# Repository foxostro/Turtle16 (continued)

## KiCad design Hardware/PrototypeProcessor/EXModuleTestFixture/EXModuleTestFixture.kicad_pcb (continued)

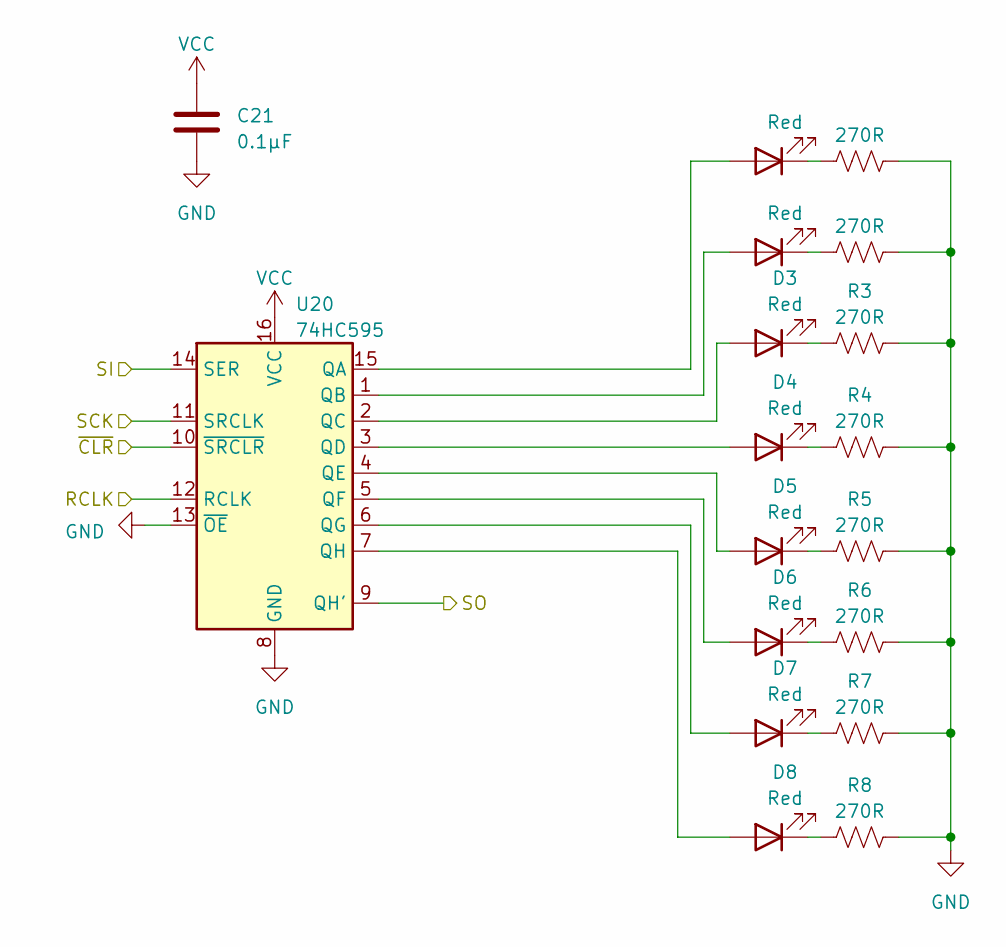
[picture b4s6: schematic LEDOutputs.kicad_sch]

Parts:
C21: 0.1µF; C_0603_1608Metric
D1, D2, D3, D4, D5, D6, D7, D8: Red; LED_0603_1608Metric
R1, R2, R3, R4, R5, R6, R7, R8: 270R; C_0603_1608Metric
U20: 74HC595; TSSOP-16_4.4x5mm_P0.65mm

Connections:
/LED Output/RCLK: U20.12 (RCLK); also elsewhere on the board
/LED Output/SCK: U20.11 (SRCLK); also elsewhere on the board
/LED Output/SI: U20.14 (SER); also elsewhere on the board
/LED Output/SO: U20.9 (QH')
/LED Output/~CLR: U20.10 (~SRCLR); also elsewhere on the board
GND: C21.2, R1.2, R2.2, R3.2, R4.2, R5.2, R6.2, R7.2, R8.2, U20.8 (GND), U20.13 (~OE); also elsewhere on the board
unnamed: D1.2 (A), U20.15 (QA)
unnamed: D1.1 (K), R1.1
unnamed: D2.2 (A), U20.1 (QB)
unnamed: D2.1 (K), R2.1
unnamed: D3.2 (A), U20.2 (QC)
unnamed: D3.1 (K), R3.1
unnamed: D4.2 (A), U20.3 (QD)
unnamed: D4.1 (K), R4.1
unnamed: D5.2 (A), U20.4 (QE)
unnamed: D5.1 (K), R5.1
unnamed: D6.2 (A), U20.5 (QF)
unnamed: D6.1 (K), R6.1
unnamed: D7.2 (A), U20.6 (QG)
unnamed: D7.1 (K), R7.1
unnamed: D8.2 (A), U20.7 (QH)
unnamed: D8.1 (K), R8.1
VCC: C21.1, U20.16 (VCC); also elsewhere on the board

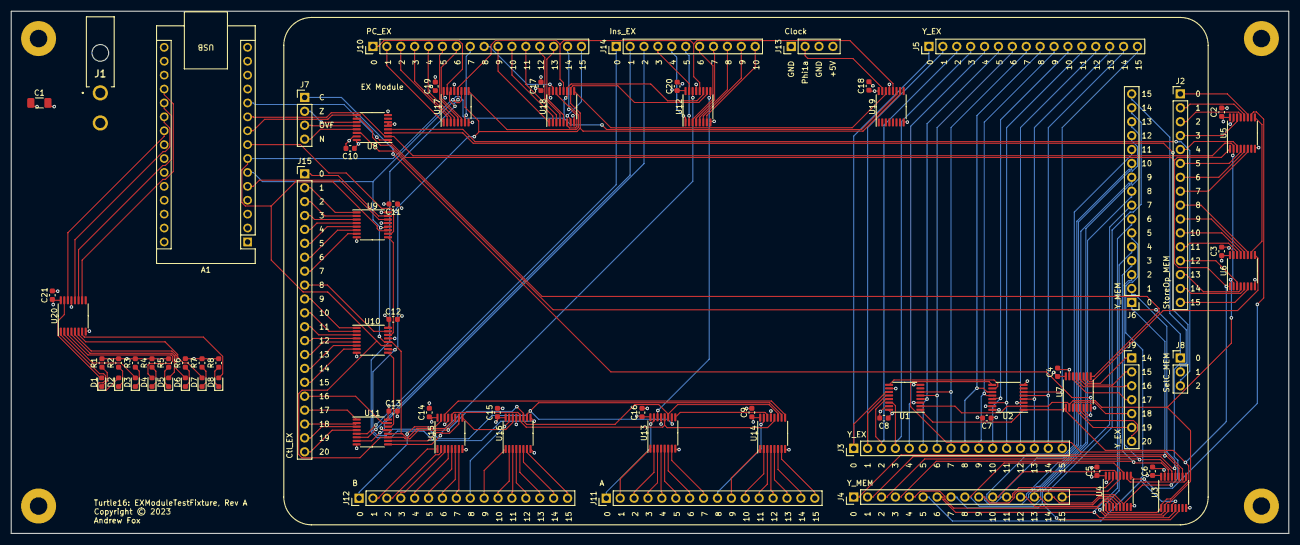
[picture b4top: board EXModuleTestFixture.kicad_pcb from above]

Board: 4 copper layers, 233.4 x 95.4 mm, 77 parts (0 on the bottom side), 189 nets.

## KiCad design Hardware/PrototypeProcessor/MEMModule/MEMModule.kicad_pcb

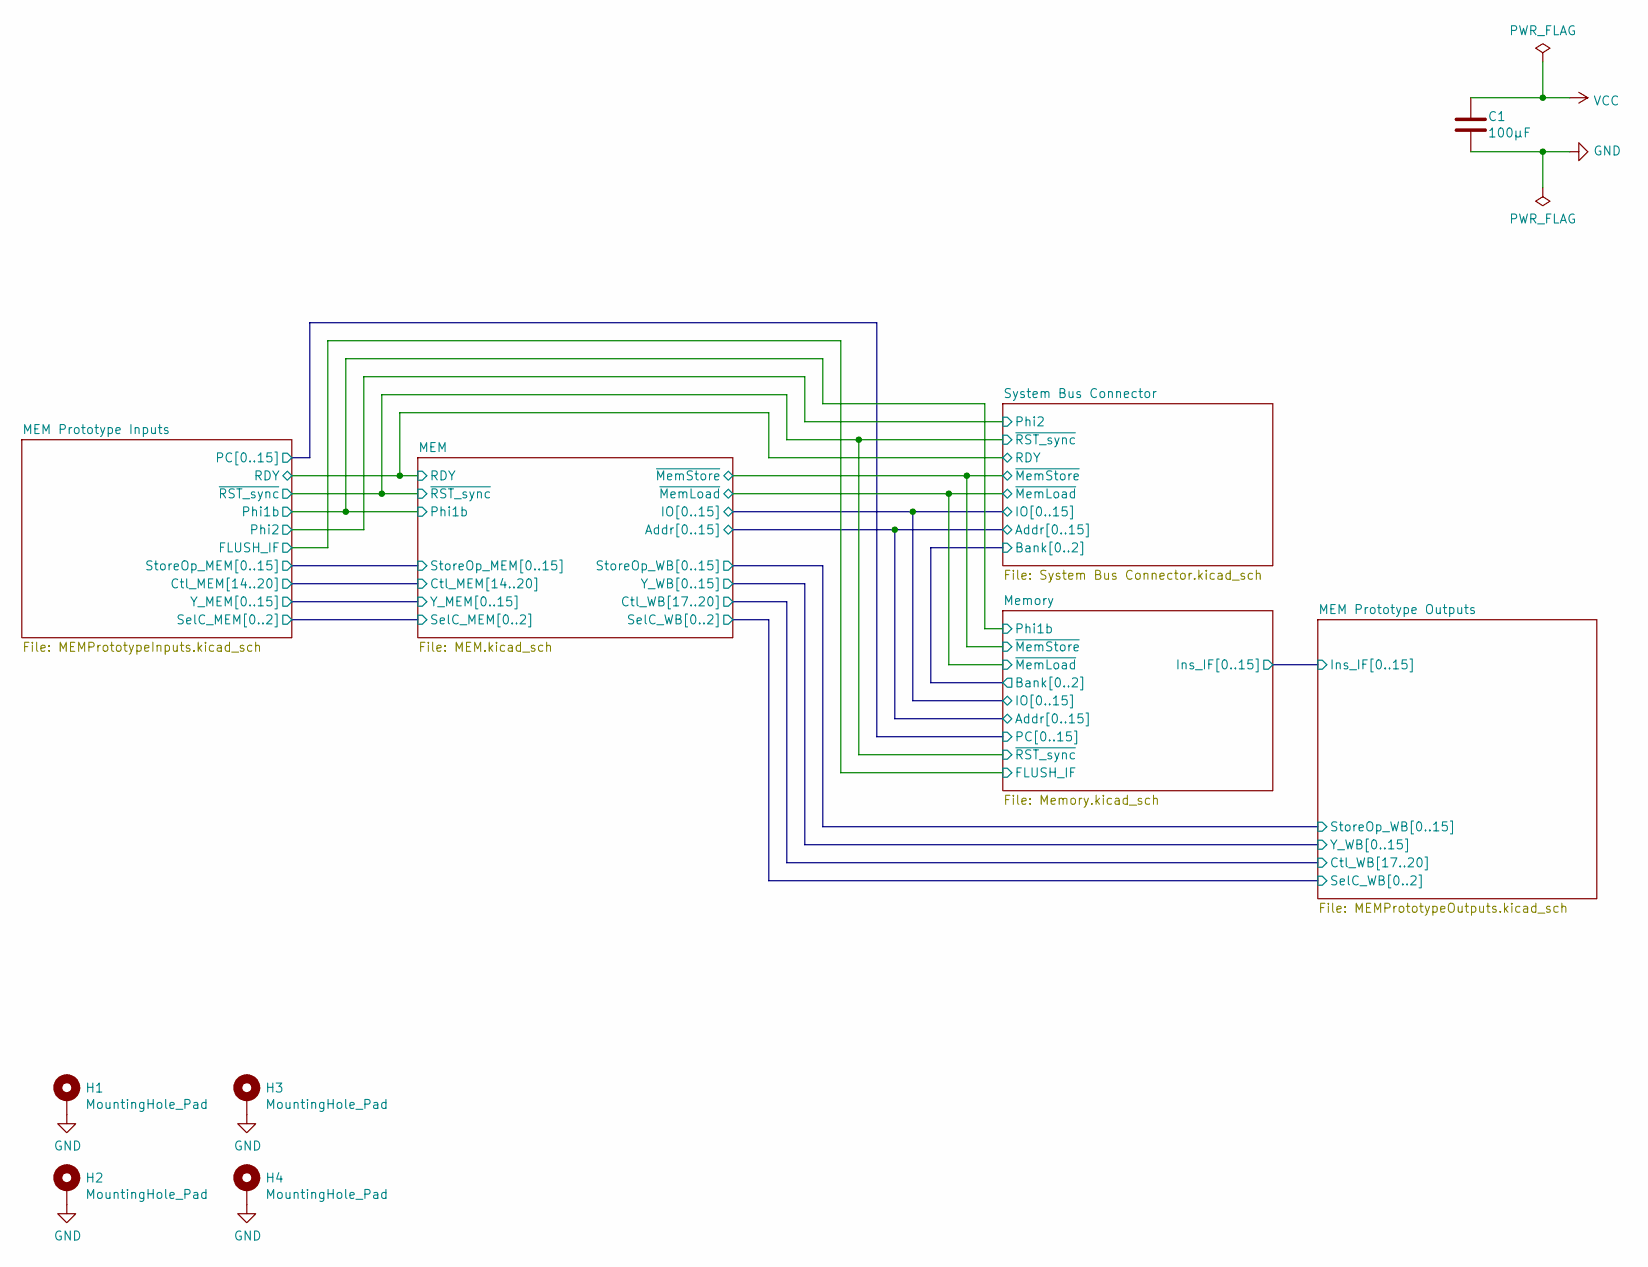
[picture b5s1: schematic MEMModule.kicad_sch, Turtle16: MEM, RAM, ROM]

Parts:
C1: 100µF; C_1206_3216Metric_Pad1.33x1.80mm_HandSolder
H1, H2, H3, H4: MountingHole_Pad; MountingHole_3.2mm_M3_Pad

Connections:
GND: C1.2, H1.1, H2.1, H3.1, H4.1; also elsewhere on the board
VCC: C1.1; also elsewhere on the board

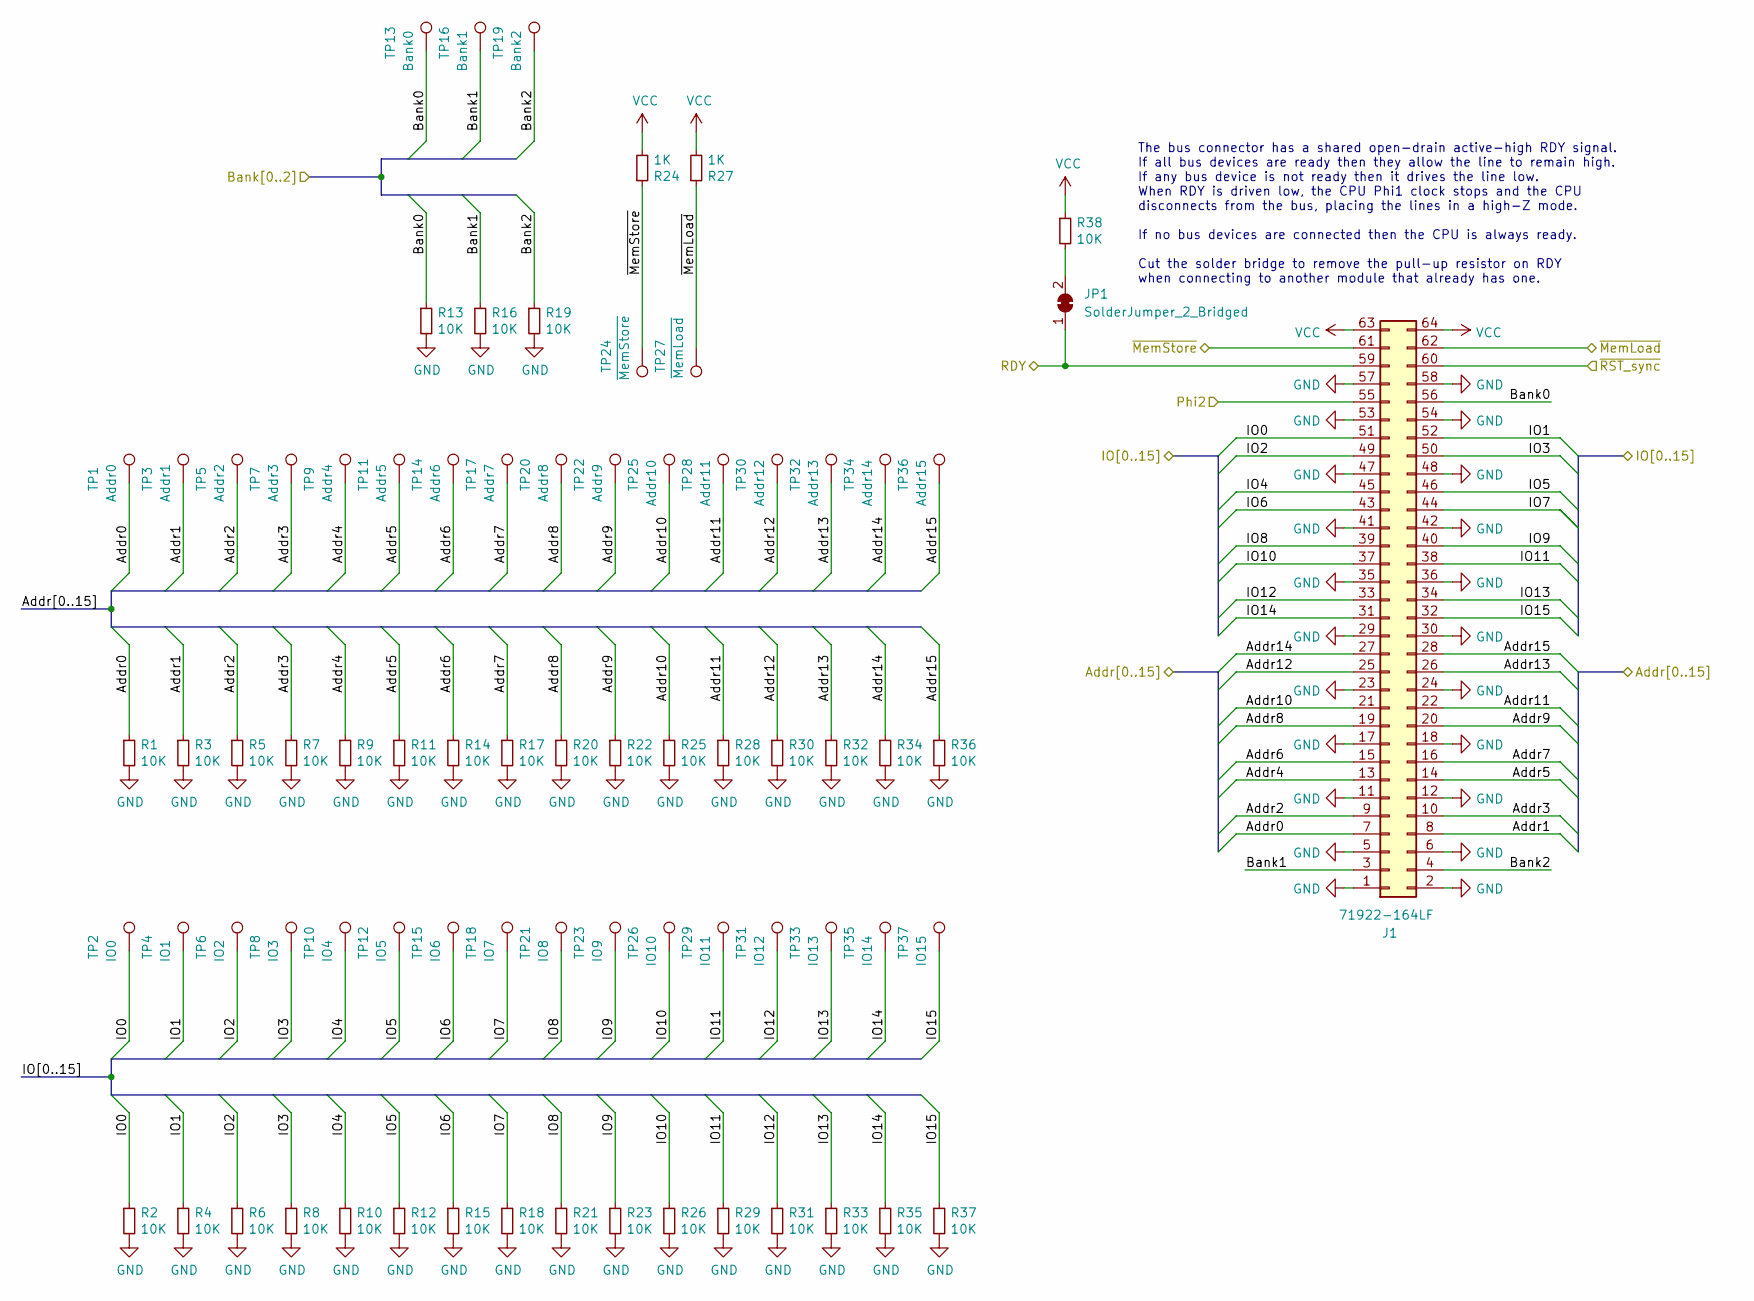
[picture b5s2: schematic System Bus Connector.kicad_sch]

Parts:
J1: 71922-164LF; IDC-Header_2x32_P2.54mm_Horizontal
JP1: SolderJumper_2_Bridged; SolderJumper-2_P1.3mm_Bridged_RoundedPad1.0x1.5mm
R1, R2, R3, R4, R5, R6, R7, R8, R9, R10, R11, R12, R13, R14, R15, R16, R17, R18, R19, R20, R21, R22, R23, R25, R26, R28, R29, R30, R31, R32, R33, R34, R35, R36, R37, R38: 10K; R_0603_1608Metric_Pad0.98x0.95mm_HandSolder
R24, R27: 1K; R_0603_1608Metric_Pad0.98x0.95mm_HandSolder
TP1: Addr0; TestPoint_Pad_D1.0mm
TP2: IO0; TestPoint_Pad_D1.0mm
TP3: Addr1; TestPoint_Pad_D1.0mm
TP4: IO1; TestPoint_Pad_D1.0mm
TP5: Addr2; TestPoint_Pad_D1.0mm
TP6: IO2; TestPoint_Pad_D1.0mm
TP7: Addr3; TestPoint_Pad_D1.0mm
TP8: IO3; TestPoint_Pad_D1.0mm
TP9: Addr4; TestPoint_Pad_D1.0mm
TP10: IO4; TestPoint_Pad_D1.0mm
TP11: Addr5; TestPoint_Pad_D1.0mm
TP12: IO5; TestPoint_Pad_D1.0mm
TP13: Bank0; TestPoint_Pad_D1.0mm
TP14: Addr6; TestPoint_Pad_D1.0mm
TP15: IO6; TestPoint_Pad_D1.0mm
TP16: Bank1; TestPoint_Pad_D1.0mm
TP17: Addr7; TestPoint_Pad_D1.0mm
TP18: IO7; TestPoint_Pad_D1.0mm
TP19: Bank2; TestPoint_Pad_D1.0mm
TP20: Addr8; TestPoint_Pad_D1.0mm
TP21: IO8; TestPoint_Pad_D1.0mm
TP22: Addr9; TestPoint_Pad_D1.0mm
TP23: IO9; TestPoint_Pad_D1.0mm
TP24: ~{MemStore}; TestPoint_Pad_D1.0mm
TP25: Addr10; TestPoint_Pad_D1.0mm
TP26: IO10; TestPoint_Pad_D1.0mm
TP27: ~{MemLoad}; TestPoint_Pad_D1.0mm
TP28: Addr11; TestPoint_Pad_D1.0mm
TP29: IO11; TestPoint_Pad_D1.0mm
TP30: Addr12; TestPoint_Pad_D1.0mm
TP31: IO12; TestPoint_Pad_D1.0mm
TP32: Addr13; TestPoint_Pad_D1.0mm
TP33: IO13; TestPoint_Pad_D1.0mm
TP34: Addr14; TestPoint_Pad_D1.0mm
TP35: IO14; TestPoint_Pad_D1.0mm
TP36: Addr15; TestPoint_Pad_D1.0mm
TP37: IO15; TestPoint_Pad_D1.0mm

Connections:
/MEM Prototype Inputs/Phi2: J1.55; also elsewhere on the board
/MEM Prototype Inputs/RDY: J1.59, JP1.1 (A); also elsewhere on the board
/MEM Prototype Inputs/~RST_sync: J1.60; also elsewhere on the board
/Memory/Addr0: J1.7, R1.1, TP1.1; also elsewhere on the board
/Memory/Addr1: J1.8, R3.1, TP3.1; also elsewhere on the board
/Memory/Addr2: J1.9, R5.1, TP5.1; also elsewhere on the board
/Memory/Addr3: J1.10, R7.1, TP7.1; also elsewhere on the board
/Memory/Addr4: J1.13, R9.1, TP9.1; also elsewhere on the board
/Memory/Addr5: J1.14, R11.1, TP11.1; also elsewhere on the board
/Memory/Addr6: J1.15, R14.1, TP14.1; also elsewhere on the board
/Memory/Addr7: J1.16, R17.1, TP17.1; also elsewhere on the board
/Memory/Addr8: J1.19, R20.1, TP20.1; also elsewhere on the board
/Memory/Addr9: J1.20, R22.1, TP22.1; also elsewhere on the board
/Memory/Addr10: J1.21, R25.1, TP25.1; also elsewhere on the board
/Memory/Addr11: J1.22, R28.1, TP28.1; also elsewhere on the board
/Memory/Addr12: J1.25, R30.1, TP30.1; also elsewhere on the board
/Memory/Addr13: J1.26, R32.1, TP32.1; also elsewhere on the board
/Memory/Addr14: J1.27, R34.1, TP34.1; also elsewhere on the board
/Memory/Addr15: J1.28, R36.1, TP36.1; also elsewhere on the board
/Memory/Bank0: J1.56, R13.1, TP13.1; also elsewhere on the board
/Memory/Bank1: J1.3, R16.1, TP16.1; also elsewhere on the board
/Memory/Bank2: J1.4, R19.1, TP19.1; also elsewhere on the board
/Memory/IO0: J1.51, R2.1, TP2.1; also elsewhere on the board
/Memory/IO1: J1.52, R4.1, TP4.1; also elsewhere on the board
/Memory/IO2: J1.49, R6.1, TP6.1; also elsewhere on the board
/Memory/IO3: J1.50, R8.1, TP8.1; also elsewhere on the board
/Memory/IO4: J1.45, R10.1, TP10.1; also elsewhere on the board
/Memory/IO5: J1.46, R12.1, TP12.1; also elsewhere on the board
/Memory/IO6: J1.43, R15.1, TP15.1; also elsewhere on the board
/Memory/IO7: J1.44, R18.1, TP18.1; also elsewhere on the board
/Memory/IO8: J1.39, R21.1, TP21.1; also elsewhere on the board
/Memory/IO9: J1.40, R23.1, TP23.1; also elsewhere on the board
/Memory/IO10: J1.37, R26.1, TP26.1; also elsewhere on the board
/Memory/IO11: J1.38, R29.1, TP29.1; also elsewhere on the board
/Memory/IO12: J1.33, R31.1, TP31.1; also elsewhere on the board
/Memory/IO13: J1.34, R33.1, TP33.1; also elsewhere on the board
/Memory/IO14: J1.31, R35.1, TP35.1; also elsewhere on the board
/Memory/IO15: J1.32, R37.1, TP37.1; also elsewhere on the board
/System Bus Connector/~MemLoad: J1.62, R27.1, TP27.1; also elsewhere on the board
/System Bus Connector/~MemStore: J1.61, R24.1, TP24.1; also elsewhere on the board
GND: J1.1, J1.2, J1.5, J1.6, J1.11, J1.12, J1.17, J1.18, J1.23, J1.24, J1.29, J1.30, J1.35, J1.36, J1.41, J1.42, J1.47, J1.48, J1.53, J1.54, J1.57, J1.58, R1.2, R2.2, R3.2, R4.2, R5.2, R6.2, R7.2, R8.2, R9.2, R10.2, R11.2, R12.2, R13.2, R14.2, R15.2, R16.2, R17.2, R18.2, R19.2, R20.2, R21.2, R22.2, R23.2, R25.2, R26.2, R28.2, R29.2, R30.2, R31.2, R32.2, R33.2, R34.2, R35.2, R36.2, R37.2; also elsewhere on the board
unnamed: JP1.2 (B), R38.2
VCC: J1.63, J1.64, R24.2, R27.2, R38.1; also elsewhere on the board

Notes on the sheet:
The bus connector has a shared open-drain active-high RDY signal. If all bus devices are ready then they allow the line to remain high. If any bus device is not ready then it drives the line low. When RDY is driven low, the CPU Phi1 clock stops and the CPU disconnects from the bus, placing the line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

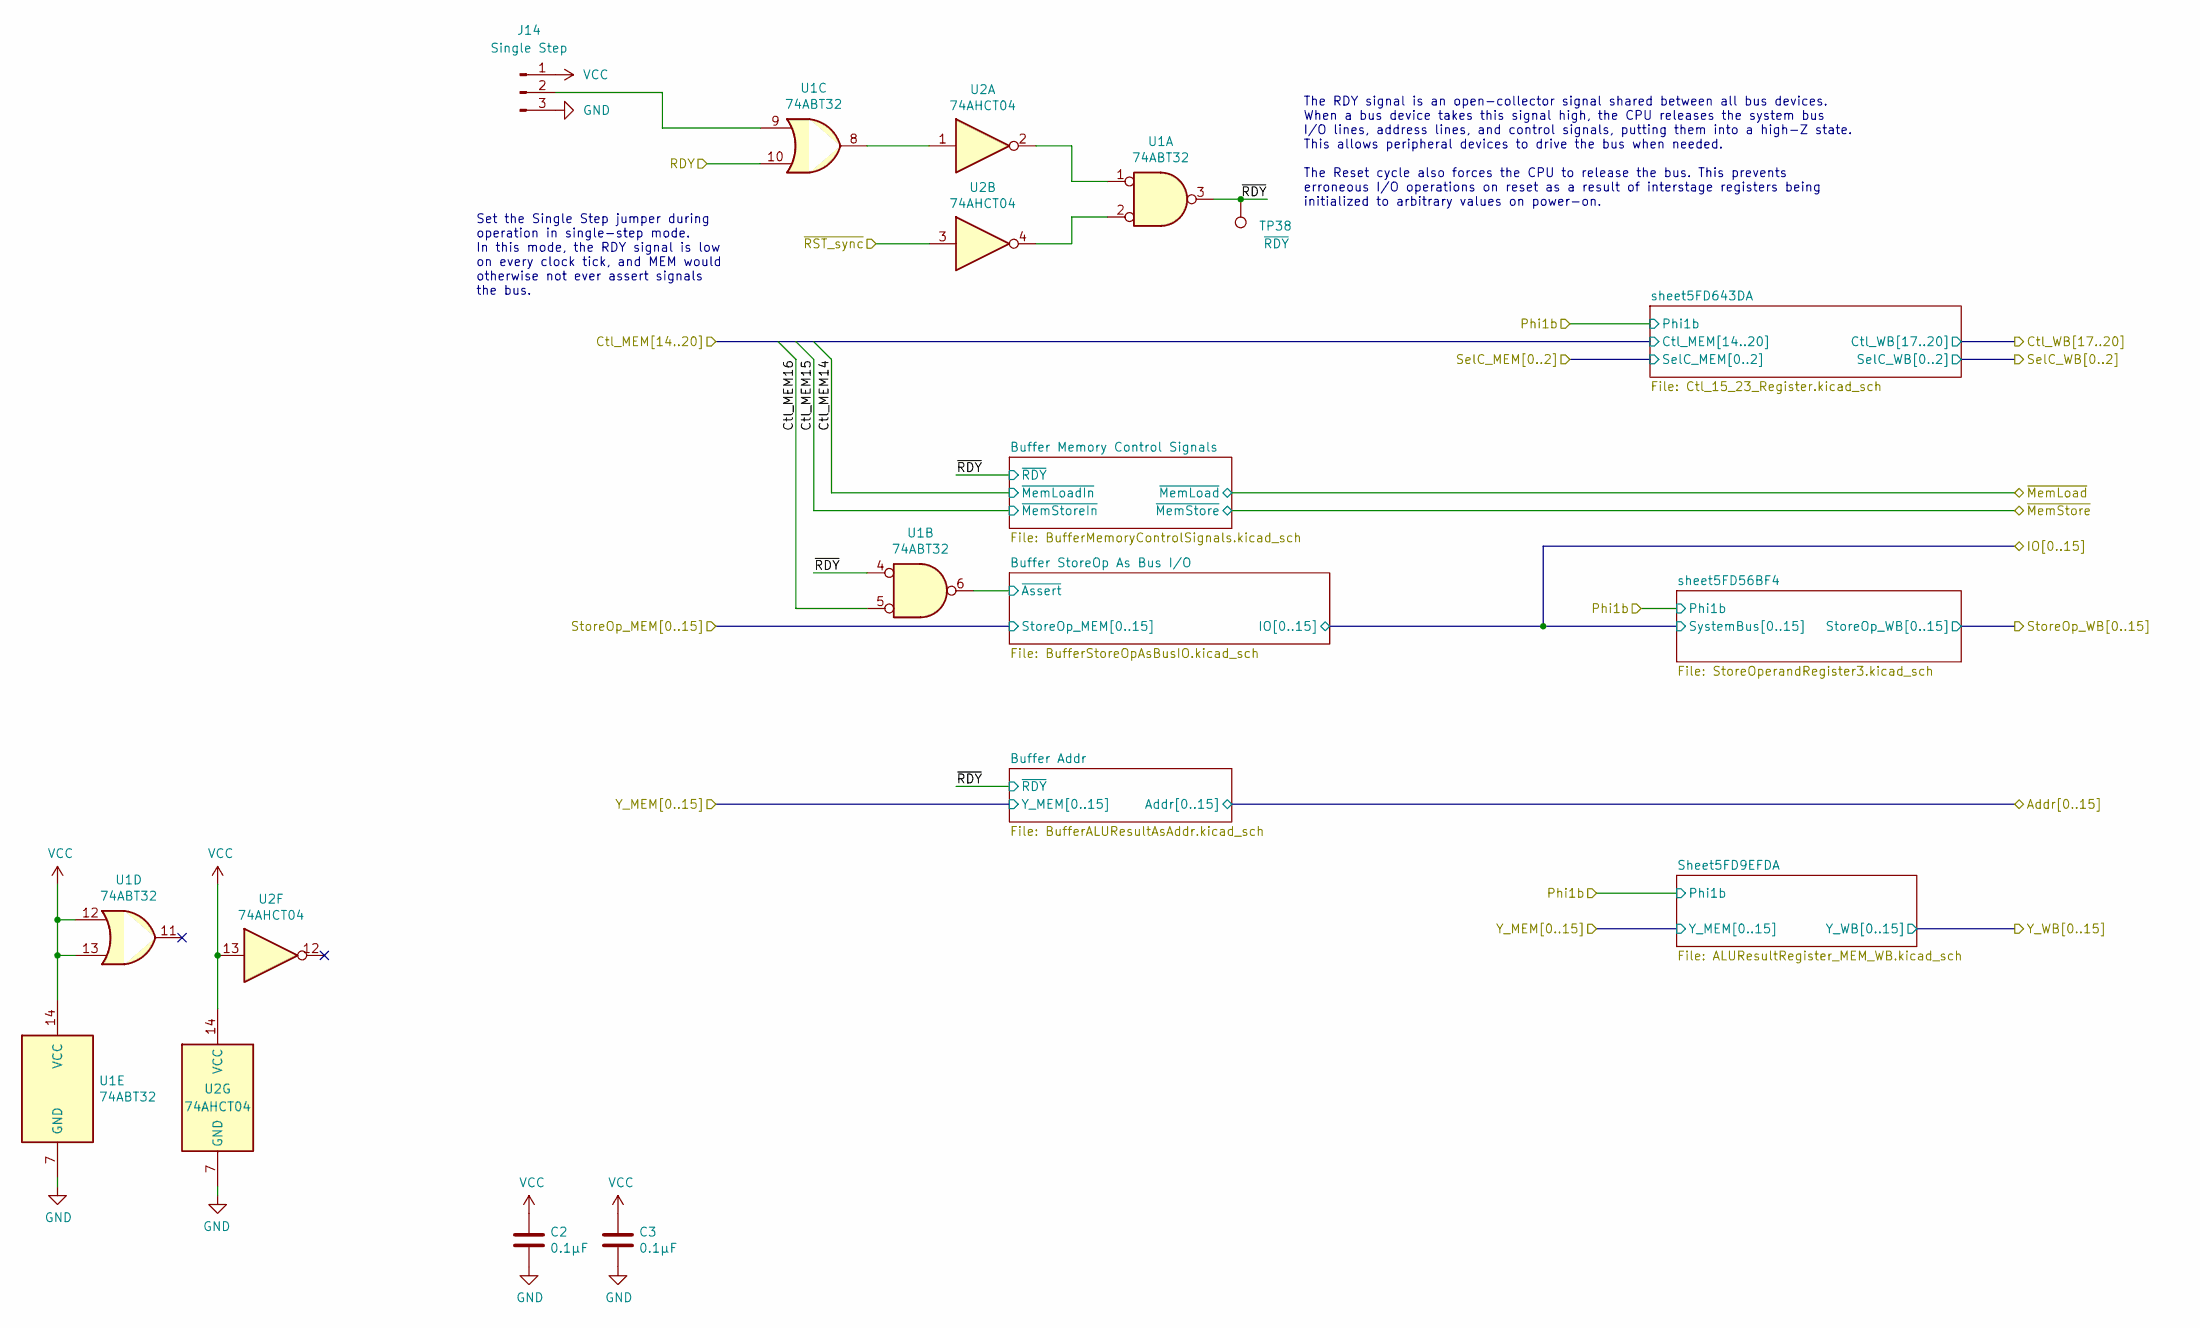
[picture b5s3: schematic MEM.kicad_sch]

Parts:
C2, C3: 0.1μF; C_0603_1608Metric_Pad1.08x0.95mm_HandSolder
J14: Single Step; PinHeader_1x03_P2.54mm_Vertical
TP38: ~{RDY}; TestPoint_Pad_D1.0mm
U1: 74ABT32; TSSOP-14_4.4x5mm_P0.65mm
U2: 74AHCT04; TSSOP-14_4.4x5mm_P0.65mm

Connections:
/MEM Prototype Inputs/Ctl_MEM16: U1.5; also elsewhere on the board
/MEM Prototype Inputs/RDY: U1.10; also elsewhere on the board
/MEM Prototype Inputs/~RST_sync: U2.3; also elsewhere on the board
/MEM/Buffer StoreOp As Bus I/O/~Assert: U1.6; also elsewhere on the board
/MEM/~RDY: TP38.1, U1.3, U1.4; also elsewhere on the board
GND: C2.2, C3.2, J14.3, U1.7 (GND), U2.7 (GND); also elsewhere on the board
unnamed: J14.2, U1.9
unnamed: U1.1, U2.2
unnamed: U1.2, U2.4
unnamed: U1.8, U2.1
VCC: C2.1, C3.1, J14.1, U1.12, U1.13, U1.14 (VCC), U2.13, U2.14 (VCC); also elsewhere on the board

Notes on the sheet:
Set the Single Step jumper during operation in single-step mode. In this mode, the RDY signal is low on every clock tick, and MEM would otherwise not ever assert signals the bus.
The RDY signal is an open-collector signal shared between all bus devices. When a bus device takes this signal high, the CPU releases the system bus I/O lines, address lines, and control signals, putting them into a high-Z state. This allows peripheral devices to drive the bus when needed. The Rese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

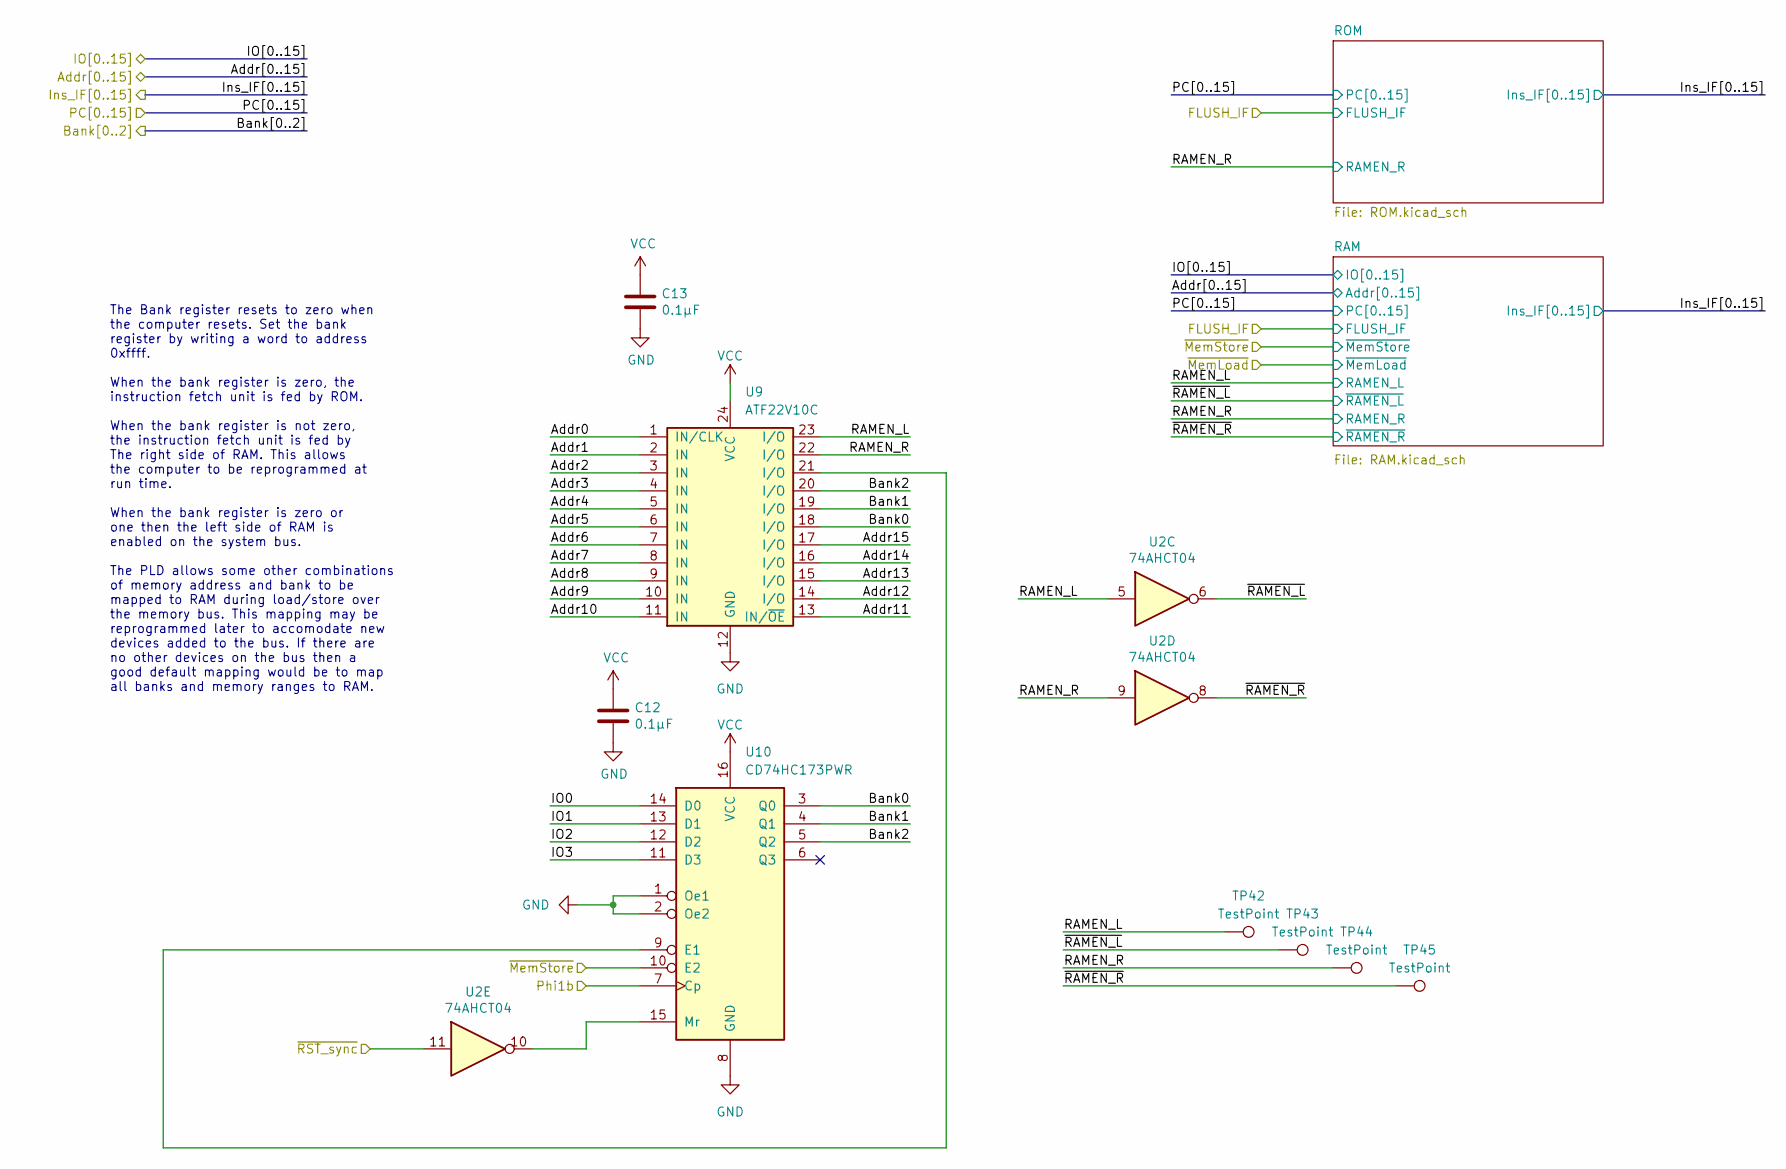
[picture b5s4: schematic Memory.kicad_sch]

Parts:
C12, C13: 0.1μF; C_0603_1608Metric_Pad1.08x0.95mm_HandSolder
TP42, TP43, TP44, TP45: TestPoint; TestPoint_Pad_D1.0mm
U2: 74AHCT04; TSSOP-14_4.4x5mm_P0.65mm
U9: ATF22V10C; DIP-24_W7.62mm_Socket
U10: CD74HC173PWR; TSSOP-16_4.4x5mm_P0.65mm

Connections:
/MEM Prototype Inputs/Phi1b: U10.7 (Cp); also elsewhere on the board
/MEM Prototype Inputs/~RST_sync: U2.11; also elsewhere on the board
/Memory/Addr0: U9.1 (IN/CLK); also elsewhere on the board
/Memory/Addr1: U9.2 (IN); also elsewhere on the board
/Memory/Addr2: U9.3 (IN); also elsewhere on the board
/Memory/Addr3: U9.4 (IN); also elsewhere on the board
/Memory/Addr4: U9.5 (IN); also elsewhere on the board
/Memory/Addr5: U9.6 (IN); also elsewhere on the board
/Memory/Addr6: U9.7 (IN); also elsewhere on the board
/Memory/Addr7: U9.8 (IN); also elsewhere on the board
/Memory/Addr8: U9.9 (IN); also elsewhere on the board
/Memory/Addr9: U9.10 (IN); also elsewhere on the board
/Memory/Addr10: U9.11 (IN); also elsewhere on the board
/Memory/Addr11: U9.13 (IN/~OE); also elsewhere on the board
/Memory/Addr12: U9.14 (I/O); also elsewhere on the board
/Memory/Addr13: U9.15 (I/O); also elsewhere on the board
/Memory/Addr14: U9.16 (I/O); also elsewhere on the board
/Memory/Addr15: U9.17 (I/O); also elsewhere on the board
/Memory/Bank0: U9.18 (I/O), U10.3 (Q0); also elsewhere on the board
/Memory/Bank1: U9.19 (I/O), U10.4 (Q1); also elsewhere on the board
/Memory/Bank2: U9.20 (I/O), U10.5 (Q2); also elsewhere on the board
/Memory/IO0: U10.14 (D0); also elsewhere on the board
/Memory/IO1: U10.13 (D1); also elsewhere on the board
/Memory/IO2: U10.12 (D2); also elsewhere on the board
/Memory/IO3: U10.11 (D3); also elsewhere on the board
/Memory/RAMEN_L: TP42.1, U2.5, U9.23 (I/O); also elsewhere on the board
/Memory/RAMEN_R: TP44.1, U2.9, U9.22 (I/O); also elsewhere on the board
/Memory/~RAMEN_L: TP43.1, U2.6; also elsewhere on the board
/Memory/~RAMEN_R: TP45.1, U2.8; also elsewhere on the board
/System Bus Connector/~MemStore: U10.10 (E2); also elsewhere on the board
GND: C12.2, C13.2, U9.12 (GND), U10.1 (Oe1), U10.2 (Oe2), U10.8 (GND); also elsewhere on the board
unnamed: U9.21 (I/O), U10.9 (E1)
unnamed: U2.10, U10.15 (Mr)
VCC: C12.1, C13.1, U9.24 (VCC), U10.16 (VCC); also elsewhere on the board

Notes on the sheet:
The Bank register resets to zero when the computer resets. Set the bank register by writing a word to address 0xffff. When the bank register is zero, the instruction fetch unit is fed by ROM. When the bank register is not zero, the instruction fetch unit is fed by The right side of RAM. This allows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

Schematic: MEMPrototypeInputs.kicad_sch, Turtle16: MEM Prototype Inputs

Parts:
J2: PC; PinHeader_1x16_P2.54mm_Vertical
J3: Y_MEM; PinHeader_1x16_P2.54mm_Vertical
J4: StoreOp_MEM; PinHeader_1x16_P2.54mm_Vertical
J5: Ctl_MEM; PinHeader_1x07_P2.54mm_Vertical
J6: SelC_MEM; PinHeader_1x03_P2.54mm_Vertical
J7: Control Signals; PinHeader_1x09_P2.54mm_Vertical

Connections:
/MEM Prototype Inputs/Ctl_MEM14: J5.1; also elsewhere on the board
/MEM Prototype Inputs/Ctl_MEM15: J5.2; also elsewhere on the board
/MEM Prototype Inputs/Ctl_MEM16: J5.3; also elsewhere on the board
/MEM Prototype Inputs/Ctl_MEM17: J5.4; also elsewhere on the board
/MEM Prototype Inputs/Ctl_MEM18: J5.5; also elsewhere on the board
/MEM Prototype Inputs/Ctl_MEM19: J5.6; also elsewhere on the board
/MEM Prototype Inputs/Ctl_MEM20: J5.7; also elsewhere on the board
/MEM Prototype Inputs/FLUSH_IF: J7.1; also elsewhere on the board
/MEM Prototype Inputs/Phi1b: J7.5; also elsewhere on the board
/MEM Prototype Inputs/Phi2: J7.3; also elsewhere on the board
/MEM Prototype Inputs/RDY: J7.6; also elsewhere on the board
/MEM Prototype Inputs/SelC_MEM0: J6.1; also elsewhere on the board
/MEM Prototype Inputs/SelC_MEM1: J6.2; also elsewhere on the board
/MEM Prototype Inputs/SelC_MEM2: J6.3; also elsewhere on the board
/MEM Prototype Inputs/StoreOp_MEM0: J4.1; also elsewhere on the board
/MEM Prototype Inputs/StoreOp_MEM1: J4.2; also elsewhere on the board
/MEM Prototype Inputs/StoreOp_MEM2: J4.3; also elsewhere on the board
/MEM Prototype Inputs/StoreOp_MEM3: J4.4; also elsewhere on the board
/MEM Prototype Inputs/StoreOp_MEM4: J4.5; also elsewhere on the board
/MEM Prototype Inputs/StoreOp_MEM5: J4.6; also elsewhere on the board
/MEM Prototype Inputs/StoreOp_MEM6: J4.7; also elsewhere on the board
/MEM Prototype Inputs/StoreOp_MEM7: J4.8; also elsewhere on the board
/MEM Prototype Inputs/StoreOp_MEM8: J4.9; also elsewhere on the board
/MEM Prototype Inputs/StoreOp_MEM9: J4.10; also elsewhere on the board
/MEM Prototype Inputs/StoreOp_MEM10: J4.11; also elsewhere on the board
/MEM Prototype Inputs/StoreOp_MEM11: J4.12; also elsewhere on the board
/MEM Prototype Inputs/StoreOp_MEM12: J4.13; also elsewhere on the board
/MEM Prototype Inputs/StoreOp_MEM13: J4.14; also elsewhere on the board
/MEM Prototype Inputs/StoreOp_MEM14: J4.15; also elsewhere on the board
/MEM Prototype Inputs/StoreOp_MEM15: J4.16; also elsewhere on the board
/MEM Prototype Inputs/Y_MEM0: J3.1; also elsewhere on the board
/MEM Prototype Inputs/Y_MEM1: J3.2; also elsewhere on the board
/MEM Prototype Inputs/Y_MEM2: J3.3; also elsewhere on the board
/MEM Prototype Inputs/Y_MEM3: J3.4; also elsewhere on the board
/MEM Prototype Inputs/Y_MEM4: J3.5; also elsewhere on the board
/MEM Prototype Inputs/Y_MEM5: J3.6; also elsewhere on the board
/MEM Prototype Inputs/Y_MEM6: J3.7; also elsewhere on the board
/MEM Prototype Inputs/Y_MEM7: J3.8; also elsewhere on the board
/MEM Prototype Inputs/Y_MEM8: J3.9; also elsewhere on the board
/MEM Prototype Inputs/Y_MEM9: J3.10; also elsewhere on the board
/MEM Prototype Inputs/Y_MEM10: J3.11; also elsewhere on the board
/MEM Prototype Inputs/Y_MEM11: J3.12; also elsewhere on the board
/MEM Prototype Inputs/Y_MEM12: J3.13; also elsewhere on the board
/MEM Prototype Inputs/Y_MEM13: J3.14; also elsewhere on the board
/MEM Prototype Inputs/Y_MEM14: J3.15; also elsewhere on the board
/MEM Prototype Inputs/Y_MEM15: J3.16; also elsewhere on the board
/MEM Prototype Inputs/~RST_sync: J7.7; also elsewhere on the board
/Memory/PC0: J2.1; also elsewhere on the board
/Memory/PC1: J2.2; also elsewhere on the board
/Memory/PC2: J2.3; also elsewhere on the board
/Memory/PC3: J2.4; also elsewhere on the board
/Memory/PC4: J2.5; also elsewhere on the board
/Memory/PC5: J2.6; also elsewhere on the board
/Memory/PC6: J2.7; also elsewhere on the board
/Memory/PC7: J2.8; also elsewhere on the board
/Memory/PC8: J2.9; also elsewhere on the board
/Memory/PC9: J2.10; also elsewhere on the board
/Memory/PC10: J2.11; also elsewhere on the board
/Memory/PC11: J2.12; also elsewhere on the board
/Memory/PC12: J2.13; also elsewhere on the board
/Memory/PC13: J2.14; also elsewhere on the board
/Memory/PC14: J2.15; also elsewhere on the board
/Memory/PC15: J2.16; also elsewhere on the board
GND: J7.2, J7.4, J7.9; also elsewhere on the board
VCC: J7.8; also elsewhere on the board

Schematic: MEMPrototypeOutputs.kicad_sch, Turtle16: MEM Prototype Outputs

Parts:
J8: Ctl_WB; PinHeader_1x04_P2.54mm_Vertical
J9: Y_WB; PinHeader_1x16_P2.54mm_Vertical
J10: SelC_WB; PinHeader_1x03_P2.54mm_Vertical
J11: Ins_IF; PinHeader_1x16_P2.54mm_Vertical
J12: StoreOp_WB; PinHeader_1x16_P2.54mm_Vertical

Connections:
/MEM Prototype Outputs/Ctl_WB17: J8.1; also elsewhere on the board
/MEM Prototype Outputs/Ctl_WB18: J8.2; also elsewhere on the board
/MEM Prototype Outputs/Ctl_WB19: J8.3; also elsewhere on the board
/MEM Prototype Outputs/Ctl_WB20: J8.4; also elsewhere on the board
/MEM Prototype Outputs/SelC_WB0: J10.1; also elsewhere on the board
/MEM Prototype Outputs/SelC_WB1: J10.2; also elsewhere on the board
/MEM Prototype Outputs/SelC_WB2: J10.3; also elsewhere on the board
/MEM Prototype Outputs/StoreOp_WB0: J12.1; also elsewhere on the board
/MEM Prototype Outputs/StoreOp_WB1: J12.2; also elsewhere on the board
/MEM Prototype Outputs/StoreOp_WB2: J12.3; also elsewhere on the board
/MEM Prototype Outputs/StoreOp_WB3: J12.4; also elsewhere on the board
/MEM Prototype Outputs/StoreOp_WB4: J12.5; also elsewhere on the board
/MEM Prototype Outputs/StoreOp_WB5: J12.6; also elsewhere on the board
/MEM Prototype Outputs/StoreOp_WB6: J12.7; also elsewhere on the board
/MEM Prototype Outputs/StoreOp_WB7: J12.8; also elsewhere on the board
/MEM Prototype Outputs/StoreOp_WB8: J12.9; also elsewhere on the board
/MEM Prototype Outputs/StoreOp_WB9: J12.10; also elsewhere on the board
/MEM Prototype Outputs/StoreOp_WB10: J12.11; also elsewhere on the board
/MEM Prototype Outputs/StoreOp_WB11: J12.12; also elsewhere on the board
/MEM Prototype Outputs/StoreOp_WB12: J12.13; also elsewhere on the board
/MEM Prototype Outputs/StoreOp_WB13: J12.14; also elsewhere on the board
/MEM Prototype Outputs/StoreOp_WB14: J12.15; also elsewhere on the board
/MEM Prototype Outputs/StoreOp_WB15: J12.16; also elsewhere on the board
/MEM Prototype Outputs/Y_WB0: J9.1; also elsewhere on the board
/MEM Prototype Outputs/Y_WB1: J9.2; also elsewhere on the board
/MEM Prototype Outputs/Y_WB2: J9.3; also elsewhere on the board
/MEM Prototype Outputs/Y_WB3: J9.4; also elsewhere on the board
/MEM Prototype Outputs/Y_WB4: J9.5; also elsewhere on the board
/MEM Prototype Outputs/Y_WB5: J9.6; also elsewhere on the board
/MEM Prototype Outputs/Y_WB6: J9.7; also elsewhere on the board
/MEM Prototype Outputs/Y_WB7: J9.8; also elsewhere on the board
/MEM Prototype Outputs/Y_WB8: J9.9; also elsewhere on the board
/MEM Prototype Outputs/Y_WB9: J9.10; also elsewhere on the board
/MEM Prototype Outputs/Y_WB10: J9.11; also elsewhere on the board
/MEM Prototype Outputs/Y_WB11: J9.12; also elsewhere on the board
/MEM Prototype Outputs/Y_WB12: J9.13; also elsewhere on the board
/MEM Prototype Outputs/Y_WB13: J9.14; also elsewhere on the board
/MEM Prototype Outputs/Y_WB14: J9.15; also elsewhere on the board
/MEM Prototype Outputs/Y_WB15: J9.16; also elsewhere on the board
/Memory/Ins_IF0: J11.1; also elsewhere on the board
/Memory/Ins_IF1: J11.2; also elsewhere on the board
/Memory/Ins_IF2: J11.3; also elsewhere on the board
/Memory/Ins_IF3: J11.4; also elsewhere on the board
/Memory/Ins_IF4: J11.5; also elsewhere on the board
/Memory/Ins_IF5: J11.6; also elsewhere on the board
/Memory/Ins_IF6: J11.7; also elsewhere on the board
/Memory/Ins_IF7: J11.8; also elsewhere on the board
/Memory/Ins_IF8: J11.9; also elsewhere on the board
/Memory/Ins_IF9: J11.10; also elsewhere on the board
/Memory/Ins_IF10: J11.11; also elsewhere on the board
/Memory/Ins_IF11: J11.12; also elsewhere on the board
/Memory/Ins_IF12: J11.13; also elsewhere on the board
/Memory/Ins_IF13: J11.14; also elsewhere on the board
/Memory/Ins_IF14: J11.15; also elsewhere on the board
/Memory/Ins_IF15: J11.16; also elsewhere on the board

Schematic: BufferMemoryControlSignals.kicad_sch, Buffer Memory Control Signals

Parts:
C4: 0.1μF; C_0603_1608Metric_Pad1.08x0.95mm_HandSolder
TP39: ~{MemStoreIn}; TestPoint_Pad_D1.0mm
TP40: ~{MemLoadIn}; TestPoint_Pad_D1.0mm
U3: 74AHCT245; TSSOP-20_4.4x6.5mm_P0.65mm

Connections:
/MEM Prototype Inputs/Ctl_MEM14: TP40.1, U3.6 (A4); also elsewhere on the board
/MEM Prototype Inputs/Ctl_MEM15: TP39.1, U3.2 (A0); also elsewhere on the board
/MEM/Buffer Memory Control Signals/MemLoadMid1: U3.7 (A5), U3.14 (B4)
/MEM/Buffer Memory Control Signals/MemLoadMid2: U3.8 (A6), U3.13 (B5)
/MEM/Buffer Memory Control Signals/MemLoadMid3: U3.9 (A7), U3.12 (B6)
/MEM/Buffer Memory Control Signals/MemStoreMid1: U3.3 (A1), U3.18 (B0)
/MEM/Buffer Memory Control Signals/MemStoreMid2: U3.4 (A2), U3.17 (B1)
/MEM/Buffer Memory Control Signals/MemStoreMid3: U3.5 (A3), U3.16 (B2)
/MEM/~RDY: U3.19 (CE); also elsewhere on the board
/System Bus Connector/~MemLoad: U3.11 (B7); also elsewhere on the board
/System Bus Connector/~MemStore: U3.15 (B3); also elsewhere on the board
GND: C4.2, U3.10 (GND); also elsewhere on the board
VCC: C4.1, U3.1 (A->B), U3.20 (VCC); also elsewhere on the board

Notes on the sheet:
Loop the control signals through the bus transceiver to add a delay of about 20ns relative to the address and data signals.
